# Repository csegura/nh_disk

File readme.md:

# NorthStar Advantage Hard Disk

This repository is made with the aim of completing a HardDisk Card for the NorthStar Advantage system. 

The idea is use a microcontroller (pi pico) to emulate a disk drive, allowing the NorthStar Advantage to read and write to a disk image stored on an SD card.

This is an ambitious project, as the NorthStar Advantage system is quite old and has a unique architecture, but it is a fun challenge. I am an enthusiast of retro computing and I want to see if I can make this work. So any help will be welcome.

Outside sure there a lot of other enthusiasts that would like to see this project completed, so welcome to the project!

## Current status

- The project is in the early stages of development.

## Pi pico plan (code)

Continuously monitor the /SELECT line (via PIO) when /SELECT is asserted (low); and monitor the primary I/O control: 
/BRD (I/O Read), /BWR (I/O Write), /IDREQ (Board ID Read).

### Address decoding 
Capture the lower I/O address bits (IOA0–IOA3) (IOA3 is not used in HD controller) from the bus when an active cycle is detected. Get the target register.

### I/O reads 
Upon detecting an I/O read cycle (/SELECT low and /BRD low): 
- Push the captured port address (IOA0–IOA3) to the PIO's RX FIFO to notify the CPU and push the captured port address to the CPU's RX FIFO.
- Change the direction of the IOD0–IOD7 data lines to output while waiting for the CPU to write the requested data byte into the PIO's TX FIFO.
- Once the TX FIFO contains data, unblock it and drive the byte onto the IOD0–IOD7 lines.
- After /BRD goes high, change the direction of IOD0–IOD7 back to input (tristate).

### I/O writes 
Upon detecting an I/O write cycle (/SELECT low and /BWR low):
- Ensure that the IOD0–IOD7 lines are configured as inputs.
- Capture the port address (IOA0–IOA3) and push it to the RX FIFO.
- Obtain the data byte present on the IOD0–IOD7 lines.
- Push the data byte to the RX FIFO and notify the CPU.
- Wait for the /BWR signal to be deasserted (go high).

### Board ID 
Upon detecting an ID Read cycle (/SELECT low AND /IDREQ low)
- Push the relevant port address.

Once the CPU is informed take the actions read registers, read/write to sdcard.

## References

- [NorthStar Advantage ROMs dissasembly](https://github.com/dualityk/advantageroms)
- [Evan Allen's NorthStar Advantage Cards](https://github.com/abzman/Northstar-Advantage-Cards)

## Special thanks

- [Evan Allen](https://github.com/abzman) for the inspiration and initial work on the NorthStar Advantage cards and help me with the project.

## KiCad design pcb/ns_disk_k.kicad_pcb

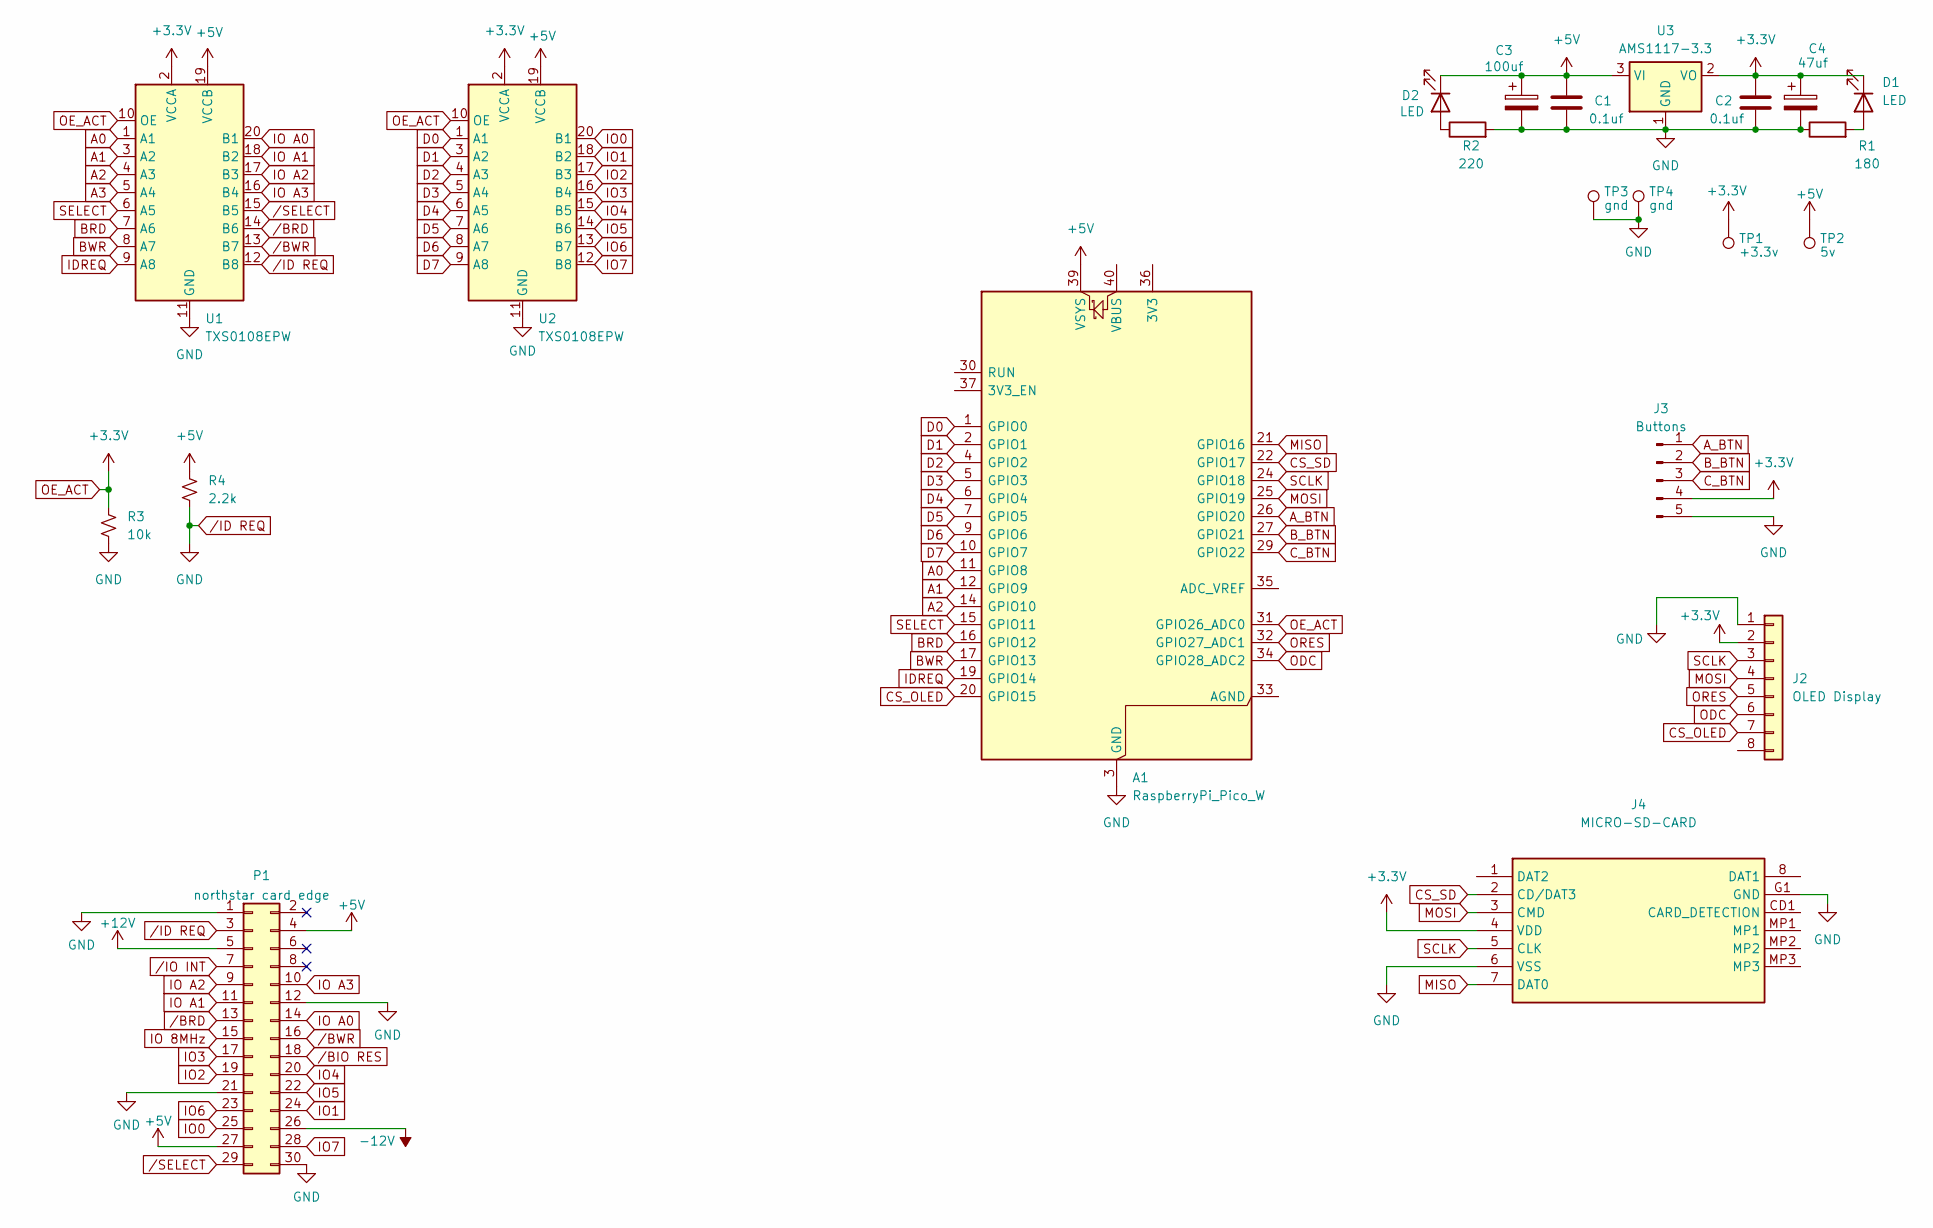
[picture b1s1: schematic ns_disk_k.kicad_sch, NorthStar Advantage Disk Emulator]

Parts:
A1: RaspberryPi_Pico_W; RaspberryPi_Pico_Common_Unspecified
C1, C2: 0.1uf; CP_EIA-1608-08_AVX-J_HandSolder
C3: 100uf; CP_EIA-3216-18_Kemet-A
C4: 47uf; CP_EIA-3216-18_Kemet-A
D1, D2: LED; LED_0402_1005Metric
J2: OLED Display; PinSocket_1x08_P2.54mm_Vertical
J3: Buttons; PinSocket_1x05_P2.54mm_Vertical
J4: MICRO-SD-CARD; MICROSDCARD; Manufacturer_Part_Number MICRO-SD-CARD; Mouser Part Number N/A
P1: northstar card edge; northstar edge connector
R1: 180; R_0805_2012Metric
R2: 220; R_0805_2012Metric
R3: 10k; R_0603_1608Metric
R4: 2.2k; R_0603_1608Metric
TP1: +3.3v; PinHeader_1x01_P2.54mm_Vertical
TP2: 5v; PinHeader_1x01_P2.54mm_Vertical
TP3, TP4: gnd; PinHeader_1x01_P2.54mm_Vertical
U1, U2: TXS0108EPW; TSSOP-20_4.4x6.5mm_P0.65mm
U3: AMS1117-3.3; SOT-223-3_TabPin2

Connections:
+5V: A1.39 (VSYS), C1.1, C3.1, D2.1 (K), P1.4, P1.27, R4.1, TP2.1, U1.19 (VCCB), U2.19 (VCCB), U3.3 (VI)
+12V: P1.5
-12V: P1.26
A0: A1.11 (GPIO8), U1.1 (A1)
A1: A1.12 (GPIO9), U1.3 (A2)
A2: A1.14 (GPIO10), U1.4 (A3)
A3: U1.5 (A4)
A_BTN: A1.26 (GPIO20), J3.1
BRD: A1.16 (GPIO12), U1.7 (A6)
BWR: A1.17 (GPIO13), U1.8 (A7)
B_BTN: A1.27 (GPIO21), J3.2
CS_OLED: A1.20 (GPIO15), J2.7
CS_SD: A1.22 (GPIO17), J4.2 (CD/DAT3)
C_BTN: A1.29 (GPIO22), J3.3
D0: A1.1 (GPIO0), U2.1 (A1)
D1: A1.2 (GPIO1), U2.3 (A2)
D2: A1.4 (GPIO2), U2.4 (A3)
D3: A1.5 (GPIO3), U2.5 (A4)
D4: A1.6 (GPIO4), U2.6 (A5)
D5: A1.7 (GPIO5), U2.7 (A6)
D6: A1.9 (GPIO6), U2.8 (A7)
D7: A1.10 (GPIO7), U2.9 (A8)
IDREQ: A1.19 (GPIO14), U1.9 (A8)
IO0: P1.25, U2.20 (B1)
IO1: P1.24, U2.18 (B2)
IO2: P1.19, U2.17 (B3)
IO3: P1.17, U2.16 (B4)
IO4: P1.20, U2.15 (B5)
IO5: P1.22, U2.14 (B6)
IO6: P1.23, U2.13 (B7)
IO7: P1.28, U2.12 (B8)
IO 8MHz: P1.15
IO A0: P1.14, U1.20 (B1)
IO A1: P1.11, U1.18 (B2)
IO A2: P1.9, U1.17 (B3)
IO A3: P1.10, U1.16 (B4)
MISO: A1.21 (GPIO16), J4.7 (DAT0)
MOSI: A1.25 (GPIO19), J2.4, J4.3 (CMD)
unnamed: D1.2 (A), R1.2
unnamed: D2.2 (A), R2.1
ODC: A1.34 (GPIO28_ADC2), J2.6
OE_ACT: A1.31 (GPIO26_ADC0), C2.1, C4.1, D1.1 (K), J2.2, J3.4, J4.4 (VDD), R3.1, TP1.1, U1.2 (VCCA), U1.10 (OE), U2.2 (VCCA), U2.10 (OE), U3.2 (VO)
ORES: A1.32 (GPIO27_ADC1), J2.5
SCLK: A1.24 (GPIO18), J2.3, J4.5 (CLK)
SELECT: A1.15 (GPIO11), U1.6 (A5)
/BIO RES: P1.18
/BRD: P1.13, U1.14 (B6)
/BWR: P1.16, U1.13 (B7)
/IO INT: P1.7
/SELECT: P1.29, U1.15 (B5)

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
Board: 2 copper layers, 22 parts (0 on the bottom side), 45 nets, no tracks yet.

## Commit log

2025-06-17 Initial
2025-06-18 - Fix /ID REQ - Re-add /SELECT - A3 remains on level shifter no on pi-pico - Added header pins for power - Added holes to pcb
